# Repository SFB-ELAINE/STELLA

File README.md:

# The SofTware dEfined impLantabLe modular plAtform (STELLA) for preclinical deep brain stimulation

## Stimulation Platform

We aimed to develop an innovative neurostimulator that significantly increases animal welfare and DBS studies' scientific value. 

Further details can be found at:

Franz Plocksties, Maria Kober, Christoph Niemann, Jakob Heller, Mareike Fauser, Martin Nüssel, Felix Uster, Denise Franz, Monique Zwar, Anika Lüttig, Justin Kröger, Jörg Harloff, Axel Schulz, Angelika Richter, Rüdiger Köhling, Dirk Timmermann, Alexander Storch:
The software defined implantable modular platform (STELLA) for preclinical deep brain stimulation research in rodents
In Journal of Neural Engineering, Vol. 18, Iss. 5, ISSN: 1741-2560, pp. 1-20, DOI: 10.1088/1741-2552/ac23e1, September 2021. https://iopscience.iop.org/article/10.1088/1741-2552/ac23e1

Hardware, software, and additional materials are available from here: [STELLA MAIN PCB](https://github.com/SFB-ELAINE/STELLA/tree/main/STELLA%20PCB)

## RF Shield

To link STELLA to the outside world, we have developed an energy-efficient RF Shield that operates in the ISM band. This shield can be piggybacked by STELLA, achieving a compact design. 

Further details can be found at:

Franz Plocksties, Obaid Ullah Shah, Felix Uster, Munawar Ali, Maximilian Koschay, Maria Kober, Alexander Storch, Dirk Timmermann:
Energy-efficient modular RF interface for fully implantable electrical devices in small rodents
In Proceedings of the IEEE Biomedical Circuits and Systems Conference (BioCAS), pp. 1-6, DOI:10.1109/BioCAS49922.2021.9645022, Berlin, Deutschland, Oktober 2021. https://ieeexplore.ieee.org/document/9645022

Hardware, software, and additional materials are available from here: [STELLA RF SHIELD](https://github.com/SFB-ELAINE/STELLA/tree/main/STELLA%20RF%20SHIELD)

## Comparison of existing neurostimulators with STELLA

|                             | Ewing (2013) [56] | Kouzani (2017) [27] | Kölbl (2016) [26] | Fluri (2017) [24] | Pinnell (2018) [29] | Adams (2019) [21] | Harnack (2008) [32] | Fleischer (2020) [57] | de Haas (2012) [31] | Hentall (2013) [33] | Millard (2007) [34]                          | Forni (2012) [25] | Alpaugh (2019) [30] | Liu (2017) [28] | Arfin (2009) [22] | STELLA                                         |
|-----------------------------|-------------------|---------------------|-------------------|-------------------|---------------------|-------------------|---------------------|-----------------------|---------------------|---------------------|----------------------------------------------|-------------------|---------------------|-----------------|-------------------|------------------------------------------------|
| Current amplitude (µA)      | 13-1000           | 200                 | 26-2036           | 10-500            | 20-2000             | -625              | 50-600              | up to 300             | 20-100              | 20-100              | 100-500                                      | 50-120            | 149                 | 200-500         | 10-1000           | 42-100                                         |
| Pulse-width (µs)            | 1µs-100% DC‡      | 90                  | 0.5µs-100% DC‡    | 60-500            | 10µs-100% DC‡       | 20 (min)          | 52                  | 60-500                | 60                  | 100-1000            | 25-250                                       | 0-80              | 103/111             | 30-1400         | 180               | 1µs-100% DC‡                                   |
| Frequency (Hz)              | 2-500             | 130                 | 10-300            | 10-200            | 0.1-5000            | 5000 (max)        | 131                 | 10-500                | 131                 | 8, 16 or 24         | 50-5000                                      | 0-130             | 130                 | 1-200           | 1400 (max)        | 10-5000                                        |
| Inter-pulse delay (µs)      | n/a               | n/a                 | 60                | n/a               | 0-pulse period      | n/a               | n/a                 | n/a                   | 200                 | n/a                 | n/a                                          | n/a               | 103                 | n/a             | n/a               | n/a                                            |
| Compliance voltage (V)      | 20                | 3 (battery)         | 17                | 3.1 (battery)     | 12                  | 10                | 18                  | 3.1 (battery)         | 4.65 (battery)      | 34                  | 5                                            | 6 (battery)       | 2,1                 | 3 (battery)     | 5                 | 2.2-2.8                                        |
| No.  of channels            | 2                 | 1                   | 1                 | 1                 | 2                   | 1                 | 1                   | 1                     | 2                   | 1                   | 1                                            | 1                 | 1                   | 1               | 4                 | 2                                              |
| Charge balancing            | Passive           | Passive             | Active            | Passive           | Active/Passive      | Active            | Active              | Passive               | Active              | Passive             | Active                                       | n/a               | Active              | Passive         | Active            | Passive                                        |
| Lifetime (DBS-on)           | 10 days           | 22 days             | 6 days            | 30 days           | 30 hours            | 9 hours           | 28 days             | 30 days               | 10 hours            | n/a (rests)         | ∞                                            | 7                 | 30 days             | 3 months        | 12 days           | 126 days (CR1216), 241 days (CR1225) ¤         |
| Type of battery             | ICP521630PM       | CR2032              | 3xp675            | 2xV364            | CR1225              | CR2032            | 2xSR48              | 2xV364                | 3xSR416             | 2xSR41              | none, energy provided through inductive cage | 2xCR1220          | 2xSR48              | CR2032          | 2xML614           | CR1216, CR1220, CR1225, CR2032□                |
| Battery weight (g)          | 5,4               | 3                   | 3x1.8             | 2x0.3             | 0.9                 | 3                 | 2x1.1               | 2x0.3                 | 3x0.13              | 2x0.6               | -                                            | 2x0.8             | 2x1.1               | 3               | 2x0.16            | 0.6 (CR1216), 0.9 (CR1225) □                   |
| PCB weight (g)              | n/a               | 0.92                | n/a               | n/a               | 0.8                 | Feb 18            | n/a                 | n/a                   | n/a                 | n/a                 | n/a                                          | n/a               | n/a                 | n/a             | n/a               | 0.6                                            |
| Total stimulator weight (g) | 11.5¶             | 4.75§               | 13.8¶             | 2.5§              | 2.8¶                | 5§                | 13¶                 | 2.8§                  | 2.1¶                | 2¶                  | 2.5{                                         | 5.6{/7.4¶         | 4.7¶                | 6§/16¶          | 1.3§              | 2.6 (CR1216),                    4 (CR1225)¶ □ |
| Battery volume (mm3)        | 3052              | 1000                | 3x550             | 2x70              | 300                 | 1000              | 2x260               | 2x70                  | 3x30                | 2x160               | -                                            | 2x250             | 2x260               | 1000            | 2x50              | 200 (CR1216),300 (CR1225) □                    |
| PCB size (mm)               | n/a               | 15x18x3*            | 26x12x3*          | n/a               | Ø12.5x5             | 30x25x3*          | 35x17.1x3*          | 10x10x1               | 25x8x3*             | n/a                 | n/a                                          | 28x9x3*           | n/a                 | Ø20x4           | 13x13x3*          | Ø13x3.3                                        |
| PCB volume (mm3)            | 2228              | 810                 | 936               | 1477              | 613                 | 2250              | 1796                | 130                   | 600                 | 688                 | n/a                                          | 756               | n/a                 | 1256            | 507               | 438                                            |
| PCB + battery volume (mm3)  | 5280              | 1810                | 2586              | 1617              | 913                 | 3250              | 2316                | 270                   | 690                 | 1008                | -                                            | 1256              | n/a                 | 2256            | 607               | 638 (CR1216),               738 (CR1225) □     |
| Total stimulator size (mm)  | 33x20x8¶          | 15x18x10*§          | 30x20x24*¶        | 21x11x7§          | Ø19.2x12.4¶         | 32.5x28x8§        | 38.5x20x13.5¶       | n/a                   | Ø8x30¶              | 18x8x7¶             | 14x12x6{                                     | 15x28x7¶          | n/a                 | Ø20x8¶          | n/a               | Ø15.5×7.5 (CR1216), Ø17.0×9.0 (CR1225)¶ □      |
| Control medium              | Magnet            | Pushbutton          | n/a               | Jumper            | Magnet              | Magnet            | Electromagn.        | Magnet                | Magnet              | Magnet              | Electromagn.                                 | n/a               | n/a                 | Electromagn.    | Electromagn.      | Magnet◆                                        |
| Output medium               | Visual LED        | Visual LED          | n/a               | Visual LED        | Visual LED          | Visual LED        | Electromagn.        | Visual LED            | IR LED              | IR LED              | Visual LED                                   | n/a               | Visual LED          | Electromagn.    | Visual LED        | Visual LED◆                                    |
| Status readout              | ♣                 | Programming status  | n/a               | On/Off/♠          | On/Off              | On/Off/♣          | Program var.        | On/Off                | On/Off/♠            | Program var.        | On/Off                                       | n/a               | ♣                   | On/Off/♣♠       | On/Off            | On/Off/♣♠◆                                     |
| Mounting                    | Head or Back      | Back                | Head              | Head              | Head                | Back              | Implant             | Implant               | Head + Implant      | Implant             | Implant + cage                               | Head              | Implant             | Head            | Head              | Implant                                        |
| Open source†                | No                | No                  | No                | No                | Complete            | No                | No                  | No                    | No                  | No                  | Incomplete                                   | No                | No                  | No              | Incomplete        | Complete                                       |

*Estimated from photographic scale <br />
‡Duty Cycle <br />
Including §battery, {housing, ¶both <br />
†Including all design/layout/firmware files and datasets for reproduction <br />
¤ Refers to the stimulation parameters (1x100 µA, 130 Hz, 60 µs) for LPM3 at a boost voltage of 3.1 V  <br />
□ Highly flexible regarding needed stimulation time and rodent’s size and weight <br />
♣Battery voltage / ♠load impedance out of range indication <br />
◆ Extendable by inter-module communication <br />

## License

This project is licensed under the terms of GNU General Public License v3.0

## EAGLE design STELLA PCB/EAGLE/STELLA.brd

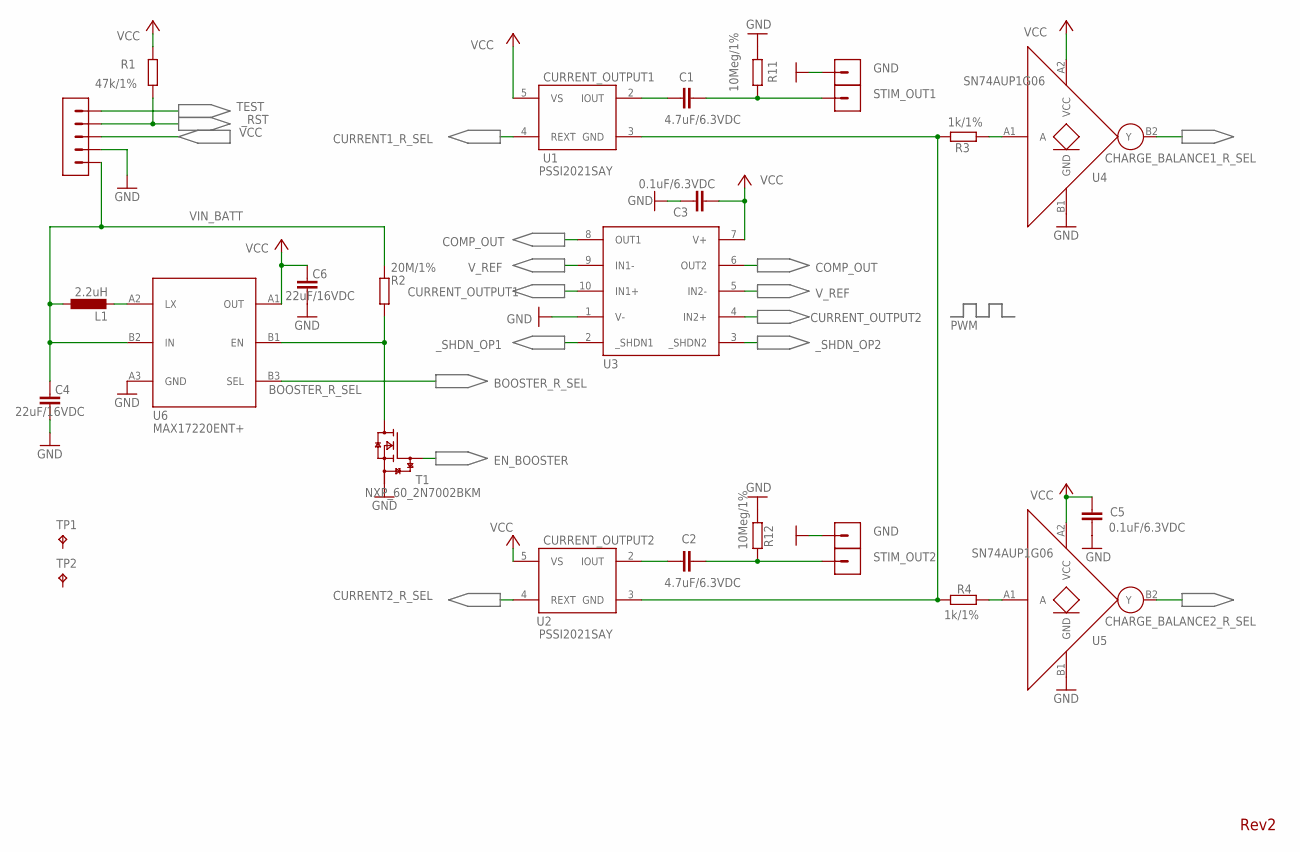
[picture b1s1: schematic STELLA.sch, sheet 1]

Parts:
C1, C2: 4.7uF/6.3VDC; C0402
C3, C5: 0.1uF/6.3VDC; C0402
C4, C6: 22uF/16VDC; MYRCL_0603
L1: 2.2uH; L0402
R1: 47k/1%; R0402
R2: 20M/1%; R0402
R3, R4: 1k/1%; R0402
R11, R12: 10Meg/1%; R0402
T1: NXP_60_2N7002BKM; NXP_60_SOT883(B)
TP1, TP2: TPTP06SQ; TP06SQ
U1, U2: PSSI2021SAY; SOT353
U3: TLV_9002S_TLV9002S_RUG
U4, U5: SN74AUP1G06; SN74AUP1G06_SN74AUP1G06YFPR
U6: MAX17220ENT+; MAX17220ENT
X1, X2, X3, X4: 1PIN_INTERFACE
X5: 5PIN; 0.9MM/0.6MM

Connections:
BOOSTER_R_SEL: U6.B3 (SEL); also elsewhere on the board
CHARGE_BALANCE1_R_SEL: U4.B2 (Y); also elsewhere on the board
CHARGE_BALANCE2_R_SEL: U5.B2 (Y); also elsewhere on the board
COMP_OUT: U3.6 (OUT2), U3.8 (OUT1); also elsewhere on the board
CURRENT1_R_SEL: U1.4 (REXT); also elsewhere on the board
CURRENT2_R_SEL: U2.4 (REXT); also elsewhere on the board
CURRENT_OUTPUT1: C1.2, U1.2 (IOUT), U3.10 (IN1+); also elsewhere on the board
CURRENT_OUTPUT2: C2.2, U2.2 (IOUT), U3.4 (IN2+); also elsewhere on the board
EN_BOOSTER: T1.1 (G); also elsewhere on the board
GND: C3.2, C4.2, C5.2, C6.2, R11.1, R12.2, T1.2 (S), U3.1 (V-), U4.B1 (GND), U5.B1 (GND), U6.A3 (GND), X2.1, X4.1, X5.2; also elsewhere on the board
unnamed: R2.1, T1.3 (D), U6.B1 (EN)
unnamed: L1.2, U6.A2 (LX)
unnamed: R3.1, U4.A1 (A)
unnamed: R4.1, U5.A1 (A)
PWM: R3.2, R4.2, U1.3 (GND), U2.3 (GND); also elsewhere on the board
STIM_OUT1: C1.1, R11.2, X1.1
STIM_OUT2: C2.1, R12.1, X3.1
TEST: X5.5; also elsewhere on the board
VCC: C3.1, C5.1, C6.1, R1.1, U1.5 (VS), U2.5 (VS), U3.7 (V+), U4.A2 (VCC), U5.A2 (VCC), U6.A1 (OUT), X5.3; also elsewhere on the board
VIN_BATT: C4.1, L1.1, R2.2, U6.B2 (IN), X5.1; also elsewhere on the board
V_REF: U3.5 (IN2-), U3.9 (IN1-); also elsewhere on the board
_RST: R1.2, X5.4; also elsewhere on the board
_SHDN_OP1: U3.2 (_SHDN1); also elsewhere on the board
_SHDN_OP2: U3.3 (_SHDN2); also elsewhere on the board

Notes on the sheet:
Rev2

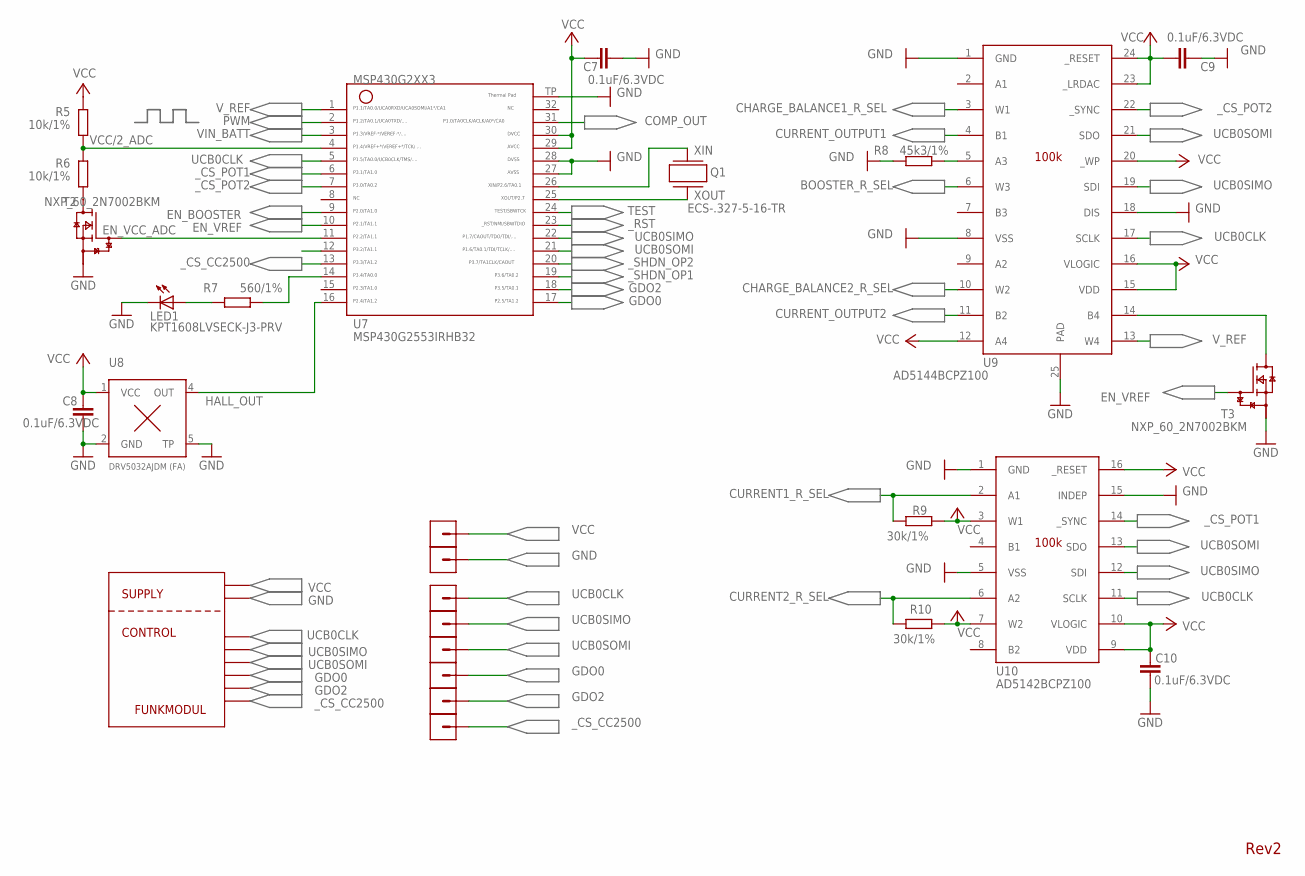
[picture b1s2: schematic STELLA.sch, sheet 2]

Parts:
C7, C8, C9, C10: 0.1uF/6.3VDC; C0402
LED1: KPT1608LVSECK-J3-PRV; LED_CHIP-LED0603
Q1: ECS-.327-5-16-TR; CRYSTAL_ECX_16_32768_ECX-16
R5, R6: 10k/1%; R0402
R7: 560/1%; R0402
R8: 45k3/1%; R0402
R9, R10: 30k/1%; R0402
T2, T3: NXP_60_2N7002BKM; NXP_60_SOT883(B)
U7: MSP430G2553IRHB32; RHB32
U8: DRV5032AJDM (FA); DRV5032_DRV5032_X2SON
U9: AD5144BCPZ100; AD5144_AD5144_LFCSP
U10: AD5142BCPZ100; AD5122_AD5142_LFCSP
X6, X7, X8, X9, X10, X11, X12, X13: 1PIN_INTERFACE

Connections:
BOOSTER_R_SEL: U9.6 (W3); also elsewhere on the board
CHARGE_BALANCE1_R_SEL: U9.3 (W1); also elsewhere on the board
CHARGE_BALANCE2_R_SEL: U9.10 (W2); also elsewhere on the board
COMP_OUT: U7.31; also elsewhere on the board
CURRENT1_R_SEL: R9.1, U10.2 (A1); also elsewhere on the board
CURRENT2_R_SEL: R10.2, U10.6 (A2); also elsewhere on the board
CURRENT_OUTPUT1: U9.4 (B1); also elsewhere on the board
CURRENT_OUTPUT2: U9.11 (B2); also elsewhere on the board
EN_BOOSTER: U7.9; also elsewhere on the board
EN_VCC_ADC: T2.1 (G), U7.11
EN_VREF: T3.1 (G), U7.10
GDO0: U7.17, X11.1
GDO2: U7.18, X12.1
GND: C7.2, C8.2, C9.1, C10.2, LED1.C, R8.2, T2.2 (S), T3.2 (S), U7.27, U7.28, U7.TP, U8.2 (GND), U8.5 (TP), U9.1 (GND), U9.8 (VSS), U9.18 (DIS), U9.25 (PAD), U10.1 (GND), U10.5 (VSS), U10.15 (INDEP), X7.1; also elsewhere on the board
HALL_OUT: U7.16, U8.4 (OUT)
unnamed: LED1.A, R7.2
unnamed: R6.2, T2.3 (D)
unnamed: R7.1, U7.14
unnamed: R8.1, U9.5 (A3)
unnamed: T3.3 (D), U9.14 (B4)
PWM: U7.2; also elsewhere on the board
TEST: U7.24; also elsewhere on the board
UCB0CLK: U7.5, U9.17 (SCLK), U10.11 (SCLK), X8.1
UCB0SIMO: U7.22, U9.19 (SDI), U10.12 (SDI), X9.1
UCB0SOMI: U7.21, U9.21 (SDO), U10.13 (SDO), X10.1
VCC: C7.1, C8.1, C9.2, C10.1, R5.1, R9.2, R10.1, U7.29, U7.30, U8.1 (VCC), U9.12 (A4), U9.15 (VDD), U9.16 (VLOGIC), U9.20 (_WP), U9.23 (_LRDAC), U9.24 (_RESET), U10.3 (W1), U10.7 (W2), U10.9 (VDD), U10.10 (VLOGIC), U10.16 (_RESET), X6.1; also elsewhere on the board
VCC/2_ADC: R5.2, R6.1, U7.4
VIN_BATT: U7.3; also elsewhere on the board
V_REF: U7.1, U9.13 (W4); also elsewhere on the board
XIN: Q1.1, U7.26
XOUT: Q1.2, U7.25
_CS_CC2500: U7.13, X13.1
_CS_POT1: U7.6, U10.14 (_SYNC)
_CS_POT2: U7.7, U9.22 (_SYNC)
_CS_POT3: U7.12
_RST: U7.23; also elsewhere on the board
_SHDN_OP1: U7.19; also elsewhere on the board
_SHDN_OP2: U7.20; also elsewhere on the board

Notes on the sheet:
100k
MSP430G2553IRHB32
ECS-.327-5-16-TR
FUNKMODUL
SUPPLY
CONTROL
VCC
GND
Rev2

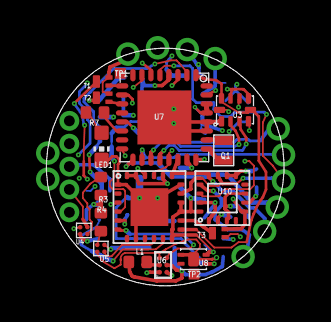
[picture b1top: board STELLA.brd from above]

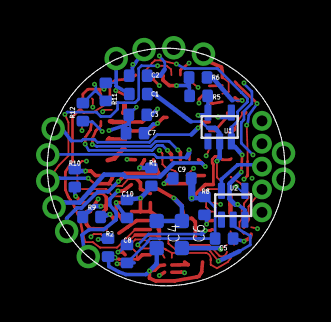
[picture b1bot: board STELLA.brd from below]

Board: 4 copper layers, 13.2 x 13.2 mm, 53 parts (21 on the bottom side), 43 nets.

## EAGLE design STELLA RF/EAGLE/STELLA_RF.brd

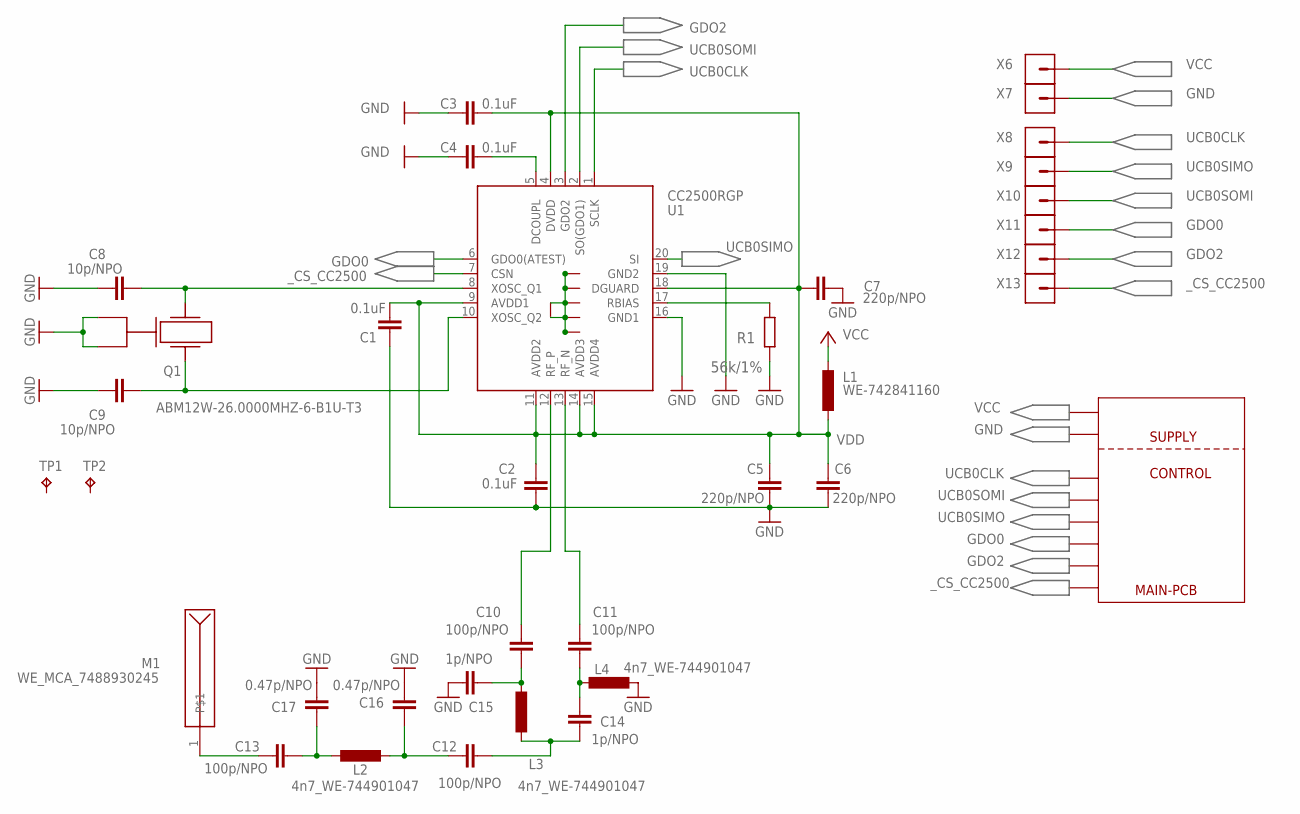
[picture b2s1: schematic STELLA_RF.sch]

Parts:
C1, C2, C3, C4: 0.1uF; C0402
C5, C6, C7: 220p/NPO; C0402
C8, C9: 10p/NPO; C0402
C10, C11, C12, C13: 100p/NPO; C0402
C14, C15: 1p/NPO; C0402
C16, C17: 0.47p/NPO; C0402
L1: WE-742841160; L0402
L2, L3, L4: 4n7_WE-744901047; L0402
M1: WE_MCA_7488930245
Q1: ABM12W-26.0000MHZ-6-B1U-T3; ABM12W
R1: 56k/1%; R0402
TP1, TP2: TPTP06SQ; TP06SQ
U1: CC2500RGP; CHIPCON_QLP20
X6, X7, X8, X9, X10, X11, X12, X13: 1PIN_INTERFACE

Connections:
GDO0: U1.6 (GDO0(ATEST)), X11.1
GDO2: U1.3 (GDO2), X12.1
GND: C1.1, C2.1, C3.1, C4.1, C5.1, C6.1, C7.2, C8.1, C9.1, C15.2, C16.2, C17.2, L4.1, Q1.2, Q1.4, R1.2, U1.16 (GND1), U1.19 (GND2), U1.EP, U1.GND1 (G1), U1.GND2 (G2), U1.GND3 (G3), U1.GND4 (G4), U1.GND5 (G5), X7.1
unnamed: C4.2, U1.5 (DCOUPL)
unnamed: C13.1, M1.1
unnamed: C8.2, Q1.1, U1.8 (XOSC_Q1)
unnamed: R1.1, U1.17 (RBIAS)
unnamed: C9.2, Q1.3, U1.10 (XOSC_Q2)
unnamed: C13.2, C17.1, L2.1
unnamed: C12.2, C16.1, L2.2
unnamed: C10.2, C15.1, L3.2
unnamed: C12.1, C14.2, L3.1
unnamed: C11.2, C14.1, L4.2
unnamed: C10.1, U1.12 (RF_P)
unnamed: C11.1, U1.13 (RF_N)
UCB0CLK: U1.1 (SCLK), X8.1
UCB0SIMO: U1.20 (SI), X9.1
UCB0SOMI: U1.2 (SO(GDO1)), X10.1
VCC: L1.1, X6.1
VDD: C1.2, C2.2, C3.2, C5.2, C6.2, C7.1, L1.2, U1.4 (DVDD), U1.9 (AVDD1), U1.11 (AVDD2), U1.14 (AVDD3), U1.15 (AVDD4), U1.18 (DGUARD)
_CS_CC2500: U1.7 (CSN), X13.1

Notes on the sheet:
WE_MCA_7488930245
SUPPLY
CONTROL
MAIN-PCB
VCC
GND
X10
X11
X12
X13

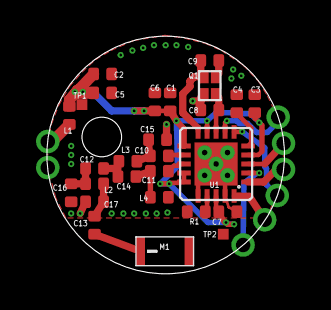
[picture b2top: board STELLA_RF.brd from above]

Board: 2 copper layers, 13.2 x 13.2 mm, 35 parts (0 on the bottom side), 21 nets.

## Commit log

2021-08-10 first add
2021-09-13 add citation information
2021-09-13 add files
2021-10-07 Add Datasets generated by STELLA
2021-10-20 add comparison table
2021-10-20 edit table
2022-01-18 add STELLA firmware
2022-10-26 edit README
2022-10-26 new add
2022-10-26 edit
2025-11-20 - Move BIST measurement point for each channel to the node before the blocking capacitor - Add a 10 MΩ discharge resistor to each output channel - Replace 100 uF capacitors with 22 uF/16VDC versions 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
